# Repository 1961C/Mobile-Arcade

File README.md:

{:height="480px"}

### Table of Contents
* [Concept](#concept)
* [System Design](#system-design)
  * [Physical Enclosure](#physical-enclosure)
  * [Arcade Emulator](#arcade-emulator)
  * [Low-level Control](#low-level-control)
    * [Drive System](#drive-system)
    * [Lighting](#lighting)
  * [Power](#power)
* [Instructions](#instructions)
* [Results](#results)
* [Improvements](#improvements)

## Concept

> "Develop a mobile arcade cabinet that can be controlled over Bluetooth to enable ultimate portability and usability, while maintaining retro charm."

The Mobile Arcade was designed to incorporate a retro gaming experience with a quirky mobile chassis. The original idea was centered around a table top arcade experience with additional entertainment features, including vibrant and responsive lighting. In order to better suit and entertain the target audience (children aged 9 through 14), mobility was incorporated as well. With this in mind, the following design requirements were set:
1. Fully functional, single player, arcade system (ability to play NES and Atari games)
2. Visually pleasing enclosure with a retro feel
3. Interactive lighting
4. Basic Bluetooth-controlled mobility

## System Design

The design of the mobile arcade was divided into distinct subsystems: the physical enclosure, the arcade emulator, the low-level drive system and lighting control. Each of these systems are outlined here.

* Raspberry Pi: Main processor
  * Handles arcade game emulator and UI
  * Interfaces with joystick and buttons
* Mbed LPC1768: Secondary processor
  * Handles lighting (LED strips)
  * Handles drive system (remotely commanded via the Bluetooth bridge)
* Dual-channel Motor Driver: Controls 2 motors in a tank-drive configuration
* Power: Li-Po battery and 5V regulator supply power to all components

### Physical Enclosure

The enclosure was designed using Dassault Systems’ Solid Works. Each portion of the seven component design was fitted together in software to ensure accurate dimensioning. The enclosure was then fabricated using 3/32" clear acrylic sheets and laser-cut at the Invention Studio.

The overall shape of the enclosure resembles that of a standard arcade cabinet, with a few notable exceptions. The design is much simpler than standard cabinets, reducing the number of distinct components that need to be fabricated. Additionally, the cabinet incorporates mounting holes near the front specifically designed to accommodate geared drive motors. Along with the rear-mounted skid, this produces a "tank drive" configuration which allows the enclosure to maneuver deftly around its environment.

{:width="640px"}

{:height="355px"}
{:height="355px"}

Holes to fit the arcade controls (joystick and buttons) and LCD screen were included. Details about each of these is covered in the next section.

### Arcade Emulator

The emulation portion of the mobile arcade was split into two portions: the physical controls and the emulation software. The raspberry pi acts as the emulation computer for this project. A small LCD screen is used and is mounted above the joystick. This LCD uses hdmi to connect to the pi.

#### _Arcade Controls_

For controlling the arcade, a standard arcade joystick configuration with four additional buttons was chosen. The following parts were acquired from Adafruit to accomplish this:

* [Joystick](https://www.adafruit.com/product/480)
* [Button](https://www.adafruit.com/product/471)
* [Control Bonnet](https://www.adafruit.com/product/3422)
* [Connection Wires](https://www.adafruit.com/product/1949)
* [Speaker](https://www.adafruit.com/product/1314)

The joystick and buttons each have a specific location they fit into within the enclosure, and were chosen before the CAD model was finalized. The control bonnet connects directly to the GPIO header on the raspberry pi and allows each of the other elements to easily interface with the emulation software. 

Once each physical element is installed, [this guide](https://learn.adafruit.com/adafruit-arcade-bonnet-for-raspberry-pi) outlines the process of formally installing the Control Bonnet on the pi. In order for it to function correctly, specific software needs to be installed on the pi. This should be done after the emulation software is installed, as outlined below.

#### _Emulation Software_

The common emulation software [RetroPie](https://retropie.org.uk/) was chosen for this project. Retropie works seamlessly with the raspberry pi, the primary processor on the mobile arcade, and offers decent functionality. Installation is made fairly easy by the fact that the Retropie foundation provides a disk image for the raspberry pi. The steps that were followed for installing the software are as follows:

1. Download the Retropie disk image from their website
2. Burn the image to the raspberry pi's SD card
3. Boot the system and connect it to the ethernet using wifi or ethernet
4. Install the Control Bonnet software (Refer to previous section)
5. Follow the automatic key-bindings dialog
6. Copy ROM files to the appropriate location

Further details about this process (excluding the Control Bonnet) can be found on the [RetroPie](https://retropie.org.uk/) website.

### Low-level Control

The Mbed microcontroller was used to implement low-level lighting and drive system control. In order to neatly connect the Mbed to the Bluetooth bridge, motor driver, and the LED strips, a single-layer PCB was designed in Eagle and fabricated at the Mechanical Engineering electronics lab. 90º headers were used so that the connections occupied minimal vertical space.

The Eagle files for the PCB can be found [here](https://github.com/1961C/Mobile-Arcade/tree/master/eagle).

Mbed code can be found [here](https://os.mbed.com/users/abraha2d/code/MobileArcade/).

{:width="640px"}

#### Drive System

The drive system consists of two motors in a tank-drive configuration, with a rear skid for stability. Wheels were added to both sides of the motors (2 visible outside, 2 hidden inside). Not only does this improve stability and ensure traction, it also adds a level of redundancy to the drive system.

A custom Mbed library was used to control the motor driver. The basic library (located [here](https://os.mbed.com/users/simon/code/Motor/)) was extended to add a short brake feature. The extended motor driver library can be found [here](https://os.mbed.com/users/abraha2d/code/Motor/).

{:width="640px"}

#### Lighting

[Dotstar LED strips](https://www.adafruit.com/product/2239) were used to implement the interactive lighting features of the Mobile Arcade. These were chosen over NeoPixels due to the standard SPI interface and relaxed timing requirements of the integrated APA102 chip, allowing for relatively easy interface with the Mbed. Since no official library was available for interfacing with the APA102, a simple library was created that fulfilled our needs (available [here](https://os.mbed.com/users/abraha2d/code/APA102/)).

The Mbed controls the LED strips in a way that simulates the actions of a real-world vehicle. Simulated lighting effects include headlights, foglights, blinkers, tail/brake lights, reverse lights, and underglow. These lighting effects are controlled in an appropriate way in relation to the movement of the enclosure.

The Mbed also accepts input from the Raspberry Pi over USB serial to synchronize lighting effects to certain events in the arcade emulator. For example, on emulation startup, a startup animation is shown on the LEDs. Other effects include a similar shutdown animation, as well as lighting theme changes when games are started/stopped.

### Power

The Mobile Arcade is powered using a wiring harness connected to a large lithium-ion battery pack. A 5V 3A regulator, connected the harness, is used to provide power for the Raspberry Pi, Mbed LPC1768, motors, and LED strips. The LCD is able to plug directly into the harness without further regulation. Fuses are integrated into the harness to protect sensitive components.

## Instructions

### Hardware setup

* Wiring harness
  * Battery power flows into a two way splitter
    * LCD Screen is powered off of one
    * 5V Regulator connects to the other
  * The 5V Regulator poweres the following items
    * Raspberry pi using a modified Micro USB Cable
    * MBed by powering its custom PCB Directly
    * Motors and LED scrips through the PCB
* Mbed PCB wiring
  * Connect 5V regulator output to power input
  * Connect DotStar LED strips to LED strip outputs
  * Connect motor leads to motor outputs
  * Insert Mbed, Bluetooth bridge, and motor driver in appropriate slots
  * Connect Mbed to Raspberry Pi with a USB cable
* Raspberry Pi Arcade Bonnet wiring ([Guide](https://learn.adafruit.com/adafruit-arcade-bonnet-for-raspberry-pi/connections))
  * Attach each button to one of the wire harness JST connector leads
  * Connect all buttons and the joystick to the Adafruit control bonnet
  * Using speaker wire, attach the speaker to the speaker header on the control bonnet

### Mbed setup

* Upload Mbed code (located [here](https://os.mbed.com/users/abraha2d/code/MobileArcade/))

### Raspberry Pi setup

* Follow RetroPie setup (located [here](retropie.org.uk))
  * Install Adafrit bonnet support software (located [here](https://learn.adafruit.com/adafruit-arcade-bonnet-for-raspberry-pi/software))
* Add runcommand scripts
  * Details about the runcommand scripts can be found [here](https://github.com/RetroPie/RetroPie-Setup/wiki/runcommand#runcommand-onstart-and-runcommand-onend-scripts)
  * Copy the files from '/runcommnads' in this repository to '/opt/retropie/configs/all/' on the raspberry pi
  * Plug the MBED into the pi using USB and ensure that the port (/dev/ttyXXXX) is correct in both runcommand files

## Results

[Demo](https://youtu.be/UGc3tqysLSs)

## Improvements

* Better connection between RPi and mBed
* Intgrate additional 5V regulator
* Add a caster to the back of the enclosure

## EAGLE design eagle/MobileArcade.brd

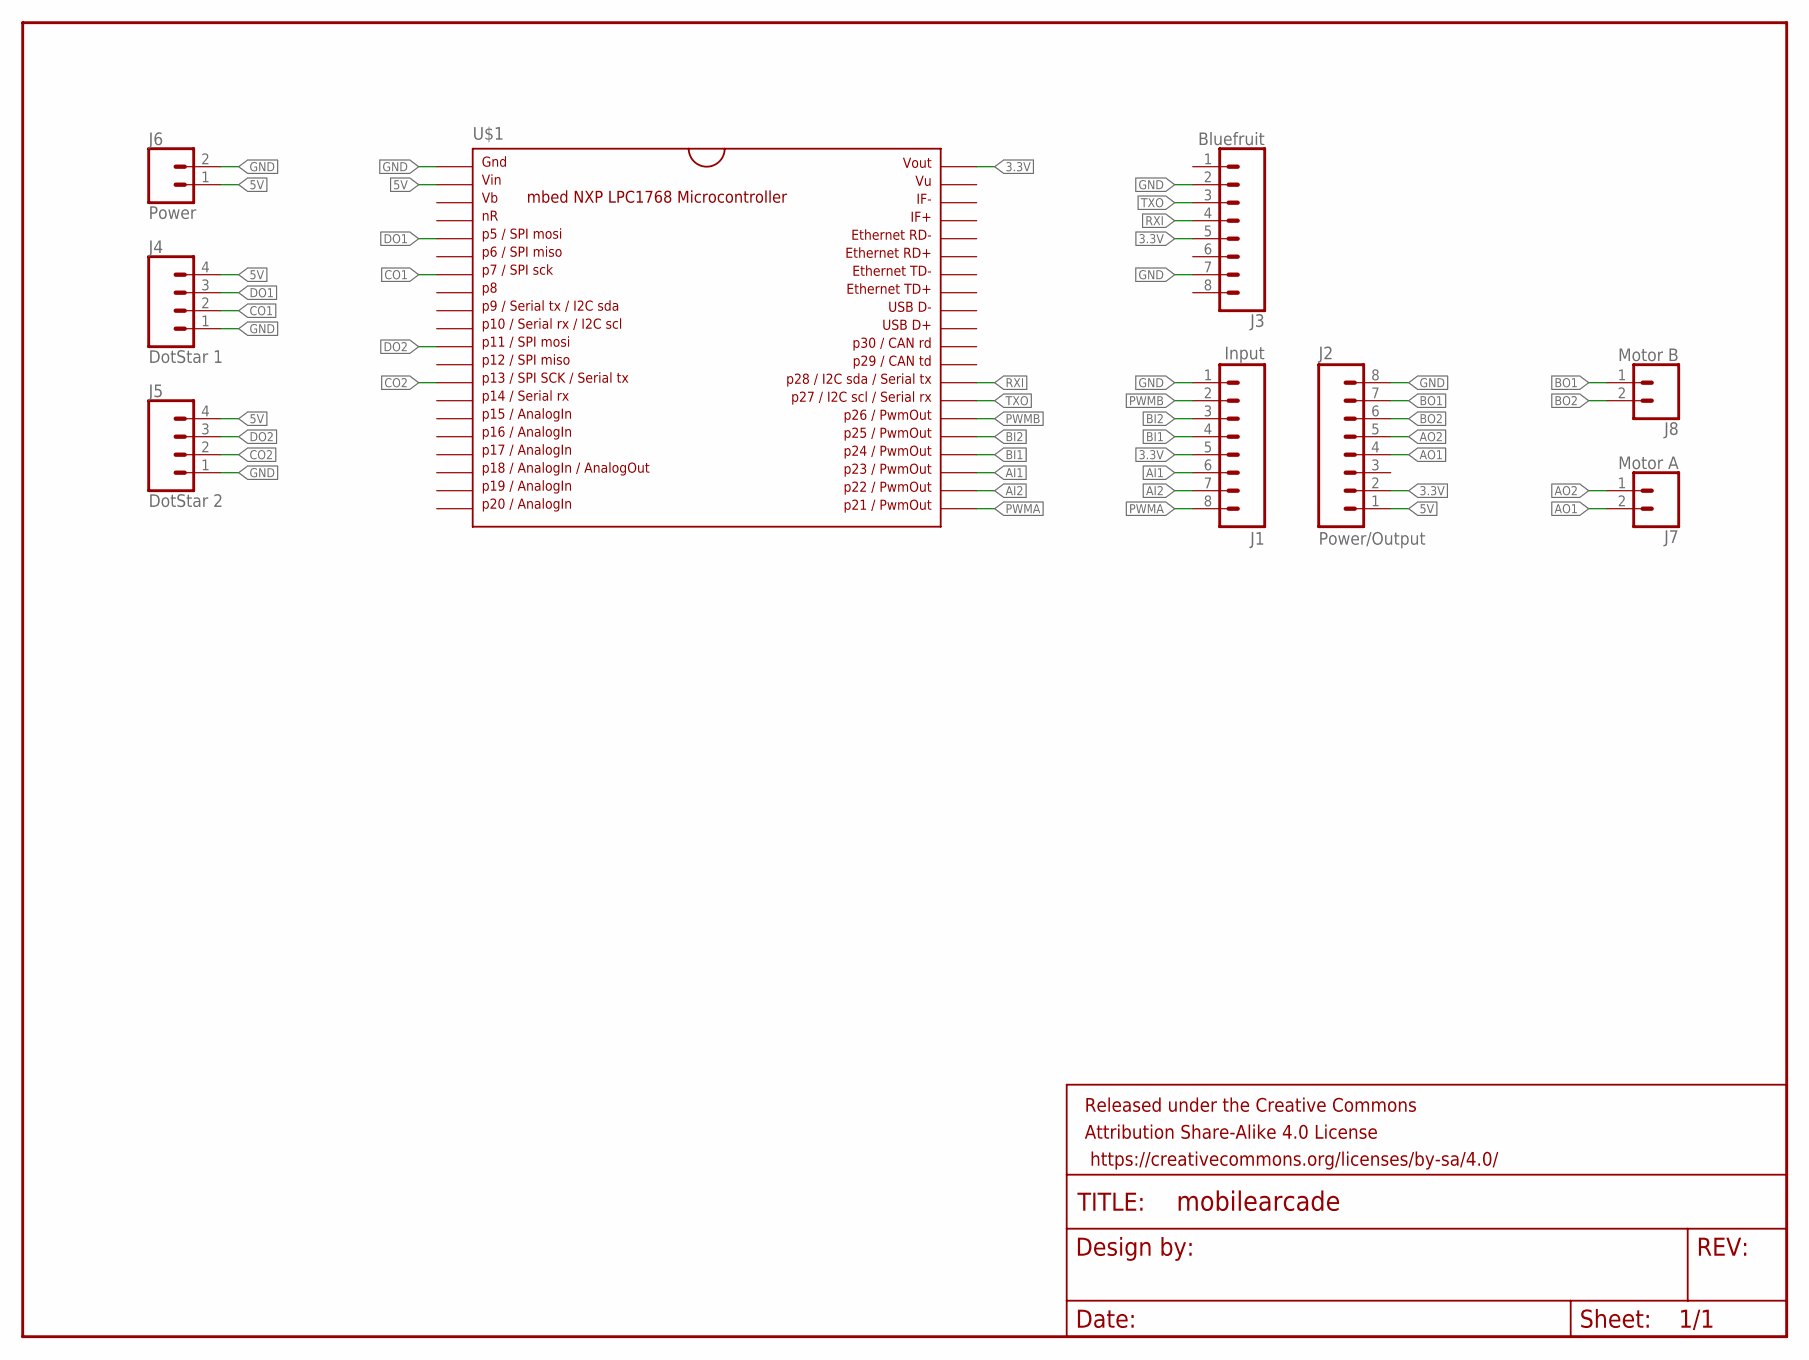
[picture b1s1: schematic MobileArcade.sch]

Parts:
FRAME1: FRAME-LETTERNO_PACKAGE; DUMMY
J1: Input; 1X08
J2: Power/Output; 1X08
J3: Bluefruit; 1X08
J4: DotStar 1; 1X04
J5: DotStar 2; 1X04
J6: Power; 1X02
J7: Motor A; 1X02
J8: Motor B; 1X02
U$1: MBED1768; DIL40_0.9

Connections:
3.3V: J1.5, J2.2, J3.5, U$1.40
5V: J2.1, J4.4, J5.4, J6.1, U$1.2
AI1: J1.6, U$1.23
AI2: J1.7, U$1.22
AO1: J2.4, J7.2
AO2: J2.5, J7.1
BI1: J1.4, U$1.24
BI2: J1.3, U$1.25
BO1: J2.7, J8.1
BO2: J2.6, J8.2
CO1: J4.2, U$1.7
CO2: J5.2, U$1.13
DO1: J4.3, U$1.5
DO2: J5.3, U$1.11
GND: J1.1, J2.8, J3.2, J3.7, J4.1, J5.1, J6.2, U$1.1
PWMA: J1.8, U$1.21
PWMB: J1.2, U$1.26
RXI: J3.4, U$1.28
TXO: J3.3, U$1.27

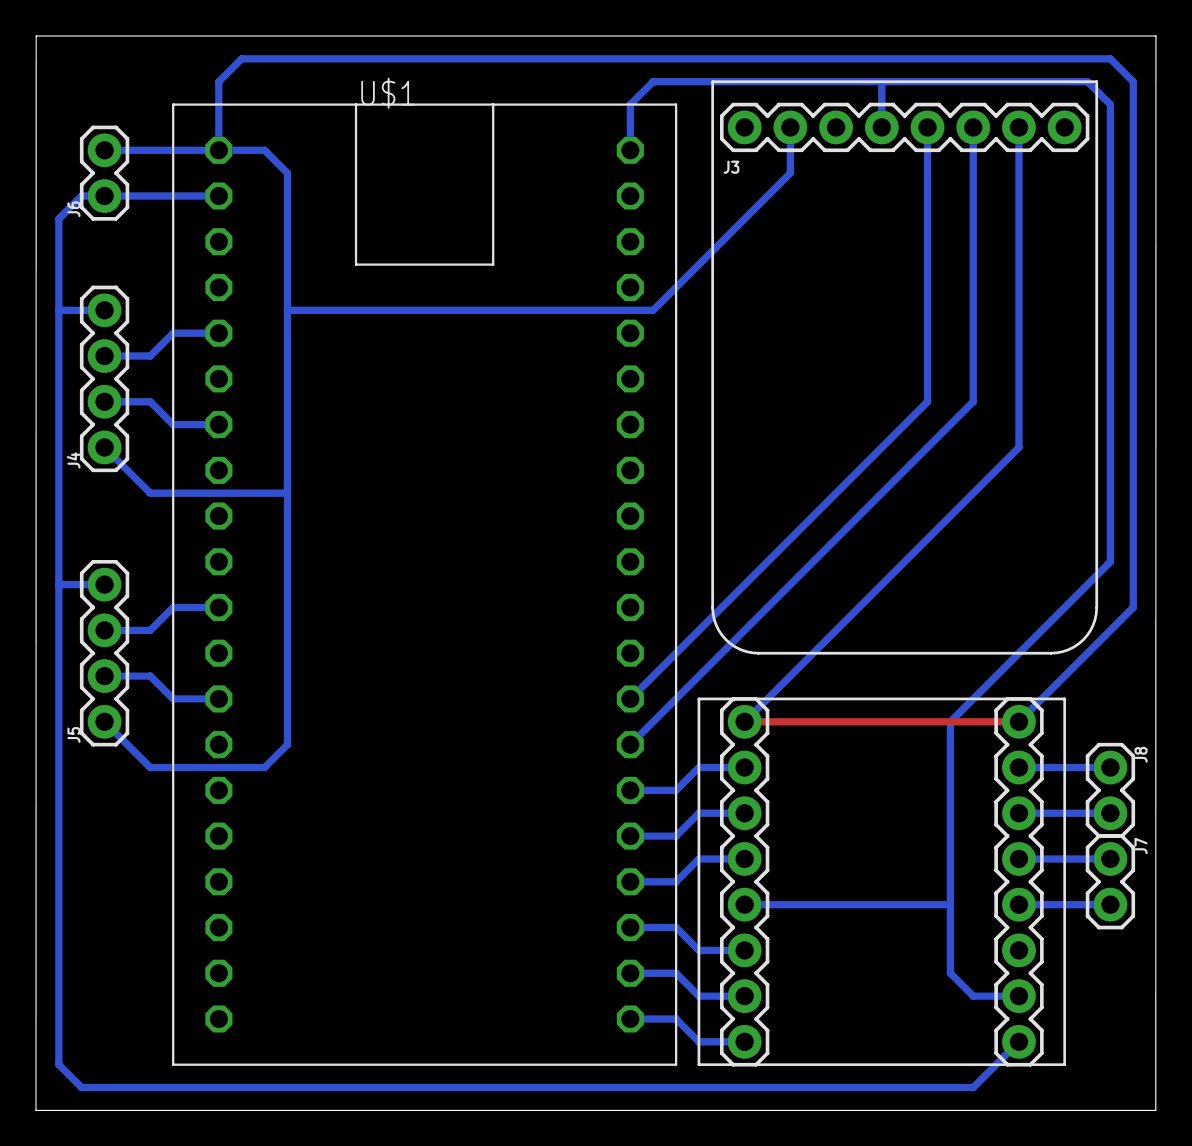
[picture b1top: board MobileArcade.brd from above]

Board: 2 copper layers, 62.2 x 59.7 mm, 10 parts (0 on the bottom side), 19 nets.

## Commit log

2018-12-10 Set theme jekyll-theme-slate
2018-12-12 Added first batch of images
2018-12-12 Added more images
2018-12-13 Added content to the design portion
2018-12-13 Fixed syntax error in the concept section
2018-12-13 Corrected some spelling
2018-12-13 Added video link
2018-12-13 Fix image links
2018-12-13 Add symlink to allow images to be displayed in both README and GitHub Pages
2018-12-13 Test new structure on one image link
2018-12-13 More image testing
2018-12-13 Update Jekyll config for images
2018-12-13 Apparently symlinks don't work that way. Poof.
2018-12-13 Update all image links
2018-12-13 Fix bullets
2018-12-13 Fix links
2018-12-13 Try resizing giant image
2018-12-13 If at first you don't succeed...
2018-12-13 Standardize the image sizes
2018-12-13 Add more complex interior view
2018-12-13 Crop interior view
2018-12-13 Add mbed pcb eagle files
2018-12-13 Fix layout of interior view pics
2018-12-13 Add eagle files to website
2018-12-13 Rework drive system section
2018-12-13 Rework ToC, add instructions
2018-12-13 Update physical enclosure section
2018-12-13 Update mbed section
2018-12-13 Update lighting section
2018-12-13 Change mbed heading
2018-12-13 Wiring harness pic doesn't add much value. Poof.
2018-12-13 Adding retropie instructions
2018-12-13 More work on the arcade setup
2018-12-13 Basic wire harness and spell check
2018-12-13 Added cad and runcommands
2018-12-13 Made folder names consistant

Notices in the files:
parts and their libraries:
SparkFun-Aesthetics: Licensing: Creative Commons ShareAlike 4.0 International - https://creativecommons.org/licenses/by-sa/4.0
SparkFun-Aesthetics: Released under the Creative Commons Attribution Share-Alike 4.0 License
SparkFun-Aesthetics: https://creativecommons.org/licenses/by-sa/4.0
